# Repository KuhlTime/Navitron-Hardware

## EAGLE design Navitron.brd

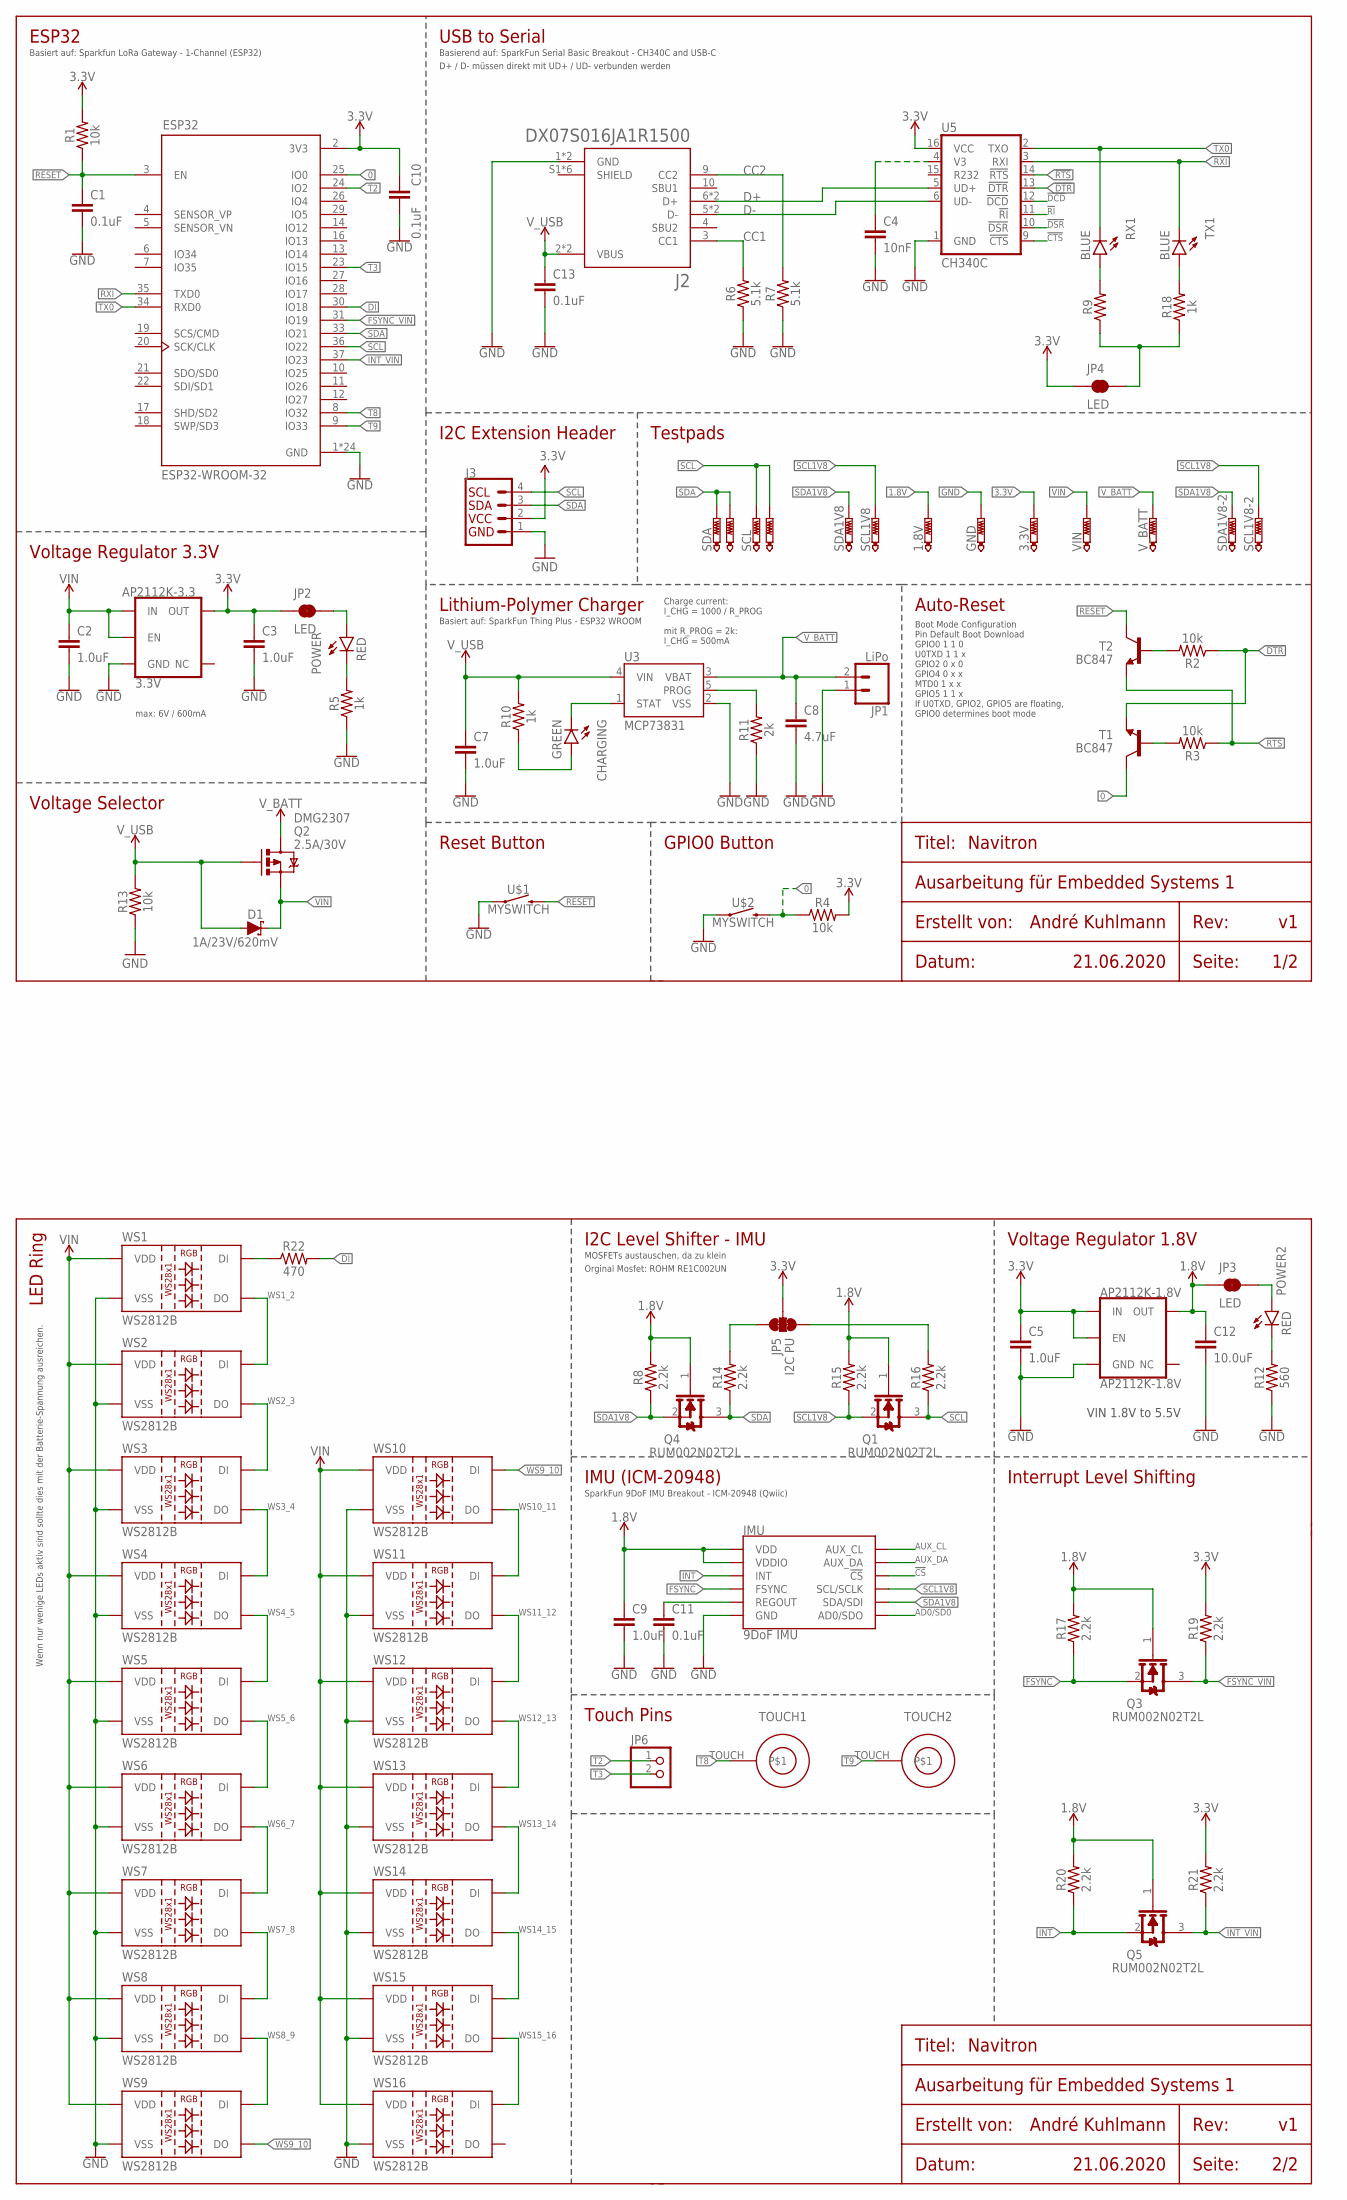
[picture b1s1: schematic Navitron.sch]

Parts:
1.8V, 3.3V: PTR1B1,27; B1,27
AP2112K-1.8V: AP2112K-1.8V; SOT23-5
AP2112K-3.3: 3.3V; SOT23-5
C1, C10, C11, C13: 0.1uF; 0603
C2, C3, C5, C7, C9: 1.0uF; 0603
C4: 10nF; 0603
C8: 4.7uF; 0603
C12: 10.0uF; 0603
CHARGING: GREEN; LED-0603
D1: 1A/23V/620mV; SOD-323
ESP32: ESP32-WROOM-32; MODULE_ESP32-WROOM-32
GND: PTR1B1,27; B1,27
IMU: 9DoF IMU; QFN24-3X3-ICM-20948
J2: DX07S016JA1R1500; JAE_DX07S016JA1R1500
J3: QWIIC_CONNECTORJS-1MM; 1X04_1MM_RA
JP1: LiPo; JST-2-SMD
JP2, JP3, JP4: LED; SMT-JUMPER_2_NC_TRACE_SILK
JP5: I2C PU; SMT-JUMPER_3_2-NC_TRACE_SILK
JP6: PINHD-1X2; 1X02
POWER, POWER2: RED; LED-0603
Q1, Q3, Q4, Q5: ROHM_RUM002N02T2LROHM_RUM002N02T2L_0_0; ROHM_RUM002N02T2L_0
Q2: 2.5A/30V; SOT23-3@1
R1, R2, R3, R4, R13: 10k; 0603
R5, R10, R18: 1k; 0603
R6, R7: 5.1k; 0603
R8, R14, R15, R16, R17, R19, R20, R21: 2.2k; 0603
R9: 10MOHM-0603-1/10W-5%; 0603
R11: 2k; 0603
R12: 560; 0603
R22: 470; 0603
RX1: BLUE; LED-0603
SCL, SCL1, SCL1V8, SCL1V8-2: PTR1B1,27; B1,27
SDA, SDA1, SDA1V8, SDA1V8-2: PTR1B1,27; B1,27
T1, T2: BC847; SOT23
TOUCH1, TOUCH2: TOUCHPAD8MM; TOUCHPAD-8MM
TX1: BLUE; LED-0603
U3: MCP73831; SOT23-5
U5: CH340C; SO016
U$1, U$2: MYSWITCH; MY-BUTTON
VIN: PTR1B1,27; B1,27
V_BATT: PTR1B1,27; B1,27
WS1, WS2, WS3, WS4, WS5, WS6, WS7, WS8, WS9, WS10, WS11, WS12, WS13, WS14, WS15, WS16: WS2812B

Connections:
0: ESP32.25 (IO0), R4.1, T1.3 (C), U$2.P$2 (2)
1.8V: 1.8V.TP, AP2112K-1.8V.5 (OUT), C9.1, C12.1, IMU.8 (VDDIO), IMU.13 (VDD), JP3.1, Q1.1 (GATE), Q3.1 (GATE), Q4.1 (GATE), Q5.1 (GATE), R8.2, R15.2, R17.2, R20.2
3.3V: 3.3V.TP, AP2112K-1.8V.1 (IN), AP2112K-1.8V.3 (EN), AP2112K-3.3.5 (OUT), C3.1, C5.1, C10.1, ESP32.2 (3V3), J3.2, JP2.1, JP4.1, JP5.2, R1.2, R4.2, R19.2, R21.2, U5.16 (VCC)
!CS: IMU.22 (!CS)
!CTS: U5.9 (!CTS)
!DCD: U5.12 (!DCD)
!DSR: U5.10 (!DSR)
!DTR: R2.1, T1.2 (E), U5.13 (!DTR)
!RI: U5.11 (!RI)
!RTS: R3.1, T2.2 (E), U5.14 (!RTS)
AD0/SD0: IMU.9 (AD0/SDO)
AUX_CL: IMU.7 (AUX_CL)
AUX_DA: IMU.21 (AUX_DA)
CC1: J2.3 (CC1), R6.2
CC2: J2.9 (CC2), R7.2
CHAR_LED_VIN: CHARGING.A, R10.1
D+: J2.6 (D+), J2.7 (D+), U5.5 (UD+)
D-: J2.5 (D-), J2.8 (D-), U5.6 (UD-)
DI: ESP32.30 (IO18), R22.2
DI_TO_WS: R22.1, WS1.4 (DI)
FSYNC: IMU.11 (FSYNC), Q3.2 (SOURCE), R17.1
FSYNC_VIN: ESP32.31 (IO19), Q3.3 (DRAIN), R19.1
GND: AP2112K-1.8V.2 (GND), AP2112K-3.3.2 (GND), C1.2, C2.2, C3.2, C4.2, C5.2, C7.2, C8.2, C9.2, C10.2, C11.2, C12.2, C13.2, ESP32.1 (GND), ESP32.15 (GND), ESP32.38 (GND), ESP32.39_1 (GND), ESP32.39_2 (GND), ESP32.39_3 (GND), ESP32.39_4 (GND), ESP32.39_5 (GND), ESP32.39_6 (GND), ESP32.39_7 (GND), ESP32.39_8 (GND), ESP32.39_9 (GND), ESP32.39_10 (GND), ESP32.39_11 (GND), ESP32.39_12 (GND), ESP32.39_13 (GND), ESP32.39_14 (GND), ESP32.39_15 (GND), ESP32.39_16 (GND), ESP32.39_17 (GND), ESP32.39_18 (GND), ESP32.39_19 (GND), ESP32.39_20 (GND), ESP32.39_21 (GND), GND.TP, IMU.18 (GND), IMU.20 (GND), J2.1 (GND), J2.12 (GND), J3.1, JP1.1 (2), R5.1, R6.1, R7.1, R11.1, R12.1, R13.1, U3.2 (VSS), U5.1 (GND), U$1.P$1 (1), U$2.P$1 (1), WS1.3 (VSS), WS2.3 (VSS), WS3.3 (VSS), WS4.3 (VSS), WS5.3 (VSS), WS6.3 (VSS), WS7.3 (VSS), WS8.3 (VSS), WS9.3 (VSS), WS10.3 (VSS), WS11.3 (VSS), WS12.3 (VSS), WS13.3 (VSS), WS14.3 (VSS), WS15.3 (VSS), WS16.3 (VSS)
INT: IMU.12 (INT), Q5.2 (SOURCE), R20.1
INT_VIN: ESP32.37 (IO23), Q5.3 (DRAIN), R21.1
LED1.8: JP3.2, POWER2.A
LED1.8_2: POWER2.C, R12.2
unnamed: POWER.C, R5.2
unnamed: JP2.2, POWER.A
PROG: R11.2, U3.5 (PROG)
REGOUT: C11.1, IMU.10 (REGOUT)
RESET: C1.1, ESP32.3 (EN), R1.1, T2.3 (C), U$1.P$2 (2)
RXI: ESP32.35 (TXD0), TX1.C, U5.3 (RXI)
SCL: ESP32.36 (IO22), J3.4, Q1.3 (DRAIN), R16.1, SCL.TP, SCL1.TP
SCL1V8: IMU.23 (SCL/SCLK), Q1.2 (SOURCE), R15.1, SCL1V8.TP, SCL1V8-2.TP
SDA: ESP32.33 (IO21), J3.3, Q4.3 (DRAIN), R14.1, SDA.TP, SDA1.TP
SDA1V8: IMU.24 (SDA/SDI), Q4.2 (SOURCE), R8.1, SDA1V8.TP, SDA1V8-2.TP
SDA_W_1: JP5.1, R14.2
SDA_W_2: JP5.3, R16.2
STAT: CHARGING.C, U3.1 (STAT)
T2: ESP32.24 (IO2), JP6.1
T3: ESP32.23 (IO15), JP6.2
T8: ESP32.8 (IO32), TOUCH1.TOUCH
T9: ESP32.9 (IO33), TOUCH2.TOUCH
TO_RX_LED: R18.2, TX1.A
TO_T1: R3.2, T1.1 (B)
TO_T2: R2.2, T2.1 (B)
TO_TX_LED: R9.2, RX1.A
TX0: ESP32.34 (RXD0), RX1.C, U5.2 (TXO)
TX_RX_LED_SUPPLY: JP4.2, R9.1, R18.1
V3_CH340: C4.1, U5.4 (V3)
VIN: AP2112K-3.3.1 (IN), AP2112K-3.3.3 (EN), C2.1, D1.C, Q2.2 (S), VIN.TP, WS1.1 (VDD), WS2.1 (VDD), WS3.1 (VDD), WS4.1 (VDD), WS5.1 (VDD), WS6.1 (VDD), WS7.1 (VDD), WS8.1 (VDD), WS9.1 (VDD), WS10.1 (VDD), WS11.1 (VDD), WS12.1 (VDD), WS13.1 (VDD), WS14.1 (VDD), WS15.1 (VDD), WS16.1 (VDD)
V_BATT: C8.1, JP1.2 (1), Q2.3 (D), U3.3 (VBAT), V_BATT.TP
V_USB: C7.1, C13.1, D1.A, J2.2 (VBUS), J2.11 (VBUS), Q2.1 (G), R10.2, R13.2, U3.4 (VIN)
WS1_2: WS1.2 (DO), WS2.4 (DI)
WS2_3: WS2.2 (DO), WS3.4 (DI)
WS3_4: WS3.2 (DO), WS4.4 (DI)
WS4_5: WS4.2 (DO), WS5.4 (DI)
WS5_6: WS5.2 (DO), WS6.4 (DI)
WS6_7: WS6.2 (DO), WS7.4 (DI)
WS7_8: WS7.2 (DO), WS8.4 (DI)
WS8_9: WS8.2 (DO), WS9.4 (DI)
WS9_10: WS9.2 (DO), WS10.4 (DI)
WS10_11: WS10.2 (DO), WS11.4 (DI)
WS11_12: WS11.2 (DO), WS12.4 (DI)
WS12_13: WS12.2 (DO), WS13.4 (DI)
WS13_14: WS13.2 (DO), WS14.4 (DI)
WS14_15: WS14.2 (DO), WS15.4 (DI)
WS15_16: WS15.2 (DO), WS16.4 (DI)

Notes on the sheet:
Seite:
1/2
Datum:
21.06.2020
Erstellt von:
André Kuhlmann
Rev:
Ausarbeitung für Embedded Systems 1
Navitron
Titel:
Boot Mode Configuration Pin Default Boot Download GPIO0 1 1 0 U0TXD 1 1 x GPIO2 0 x 0 GPIO4 0 x x MTD0 1 x x GPIO5 1 1 x If U0TXD, GPIO2, GPIO5 are floating, GPIO0 determines boot mode
Basiert auf: Sparkfun LoRa Gateway - 1-Channel (ESP32)
Voltage Regulator 3.3V
ESP32
Auto-Reset
USB to Serial
max: 6V / 600mA
D+ / D- müssen direkt mit UD+ / UD- verbunden werden
Basierend auf: SparkFun Serial Basic Breakout - CH340C and USB-C
Reset Button
GPIO0 Button
Voltage Selector
Lithium-Polymer Charger
Basiert auf: SparkFun Thing Plus - ESP32 WROOM
Charge current: I_CHG = 1000 / R_PROG mit R_PROG = 2k: I_CHG = 500mA
I2C Extension Header
VIN 1.8V to 5.5V
Voltage Regulator 1.8V
IMU (ICM-20948)
2/2
LED Ring
I2C Level Shifter - IMU
Wenn nur wenige LEDs aktiv sind sollte dies mit der Batterie-Spannung ausreichen.
MOSFETs austauschen, da zu klein
SparkFun 9DoF IMU Breakout - ICM-20948 (Qwiic)
Orginal Mosfet: ROHM RE1C002UN
Interrupt Level Shifting
Testpads
Touch Pins
DMG2307

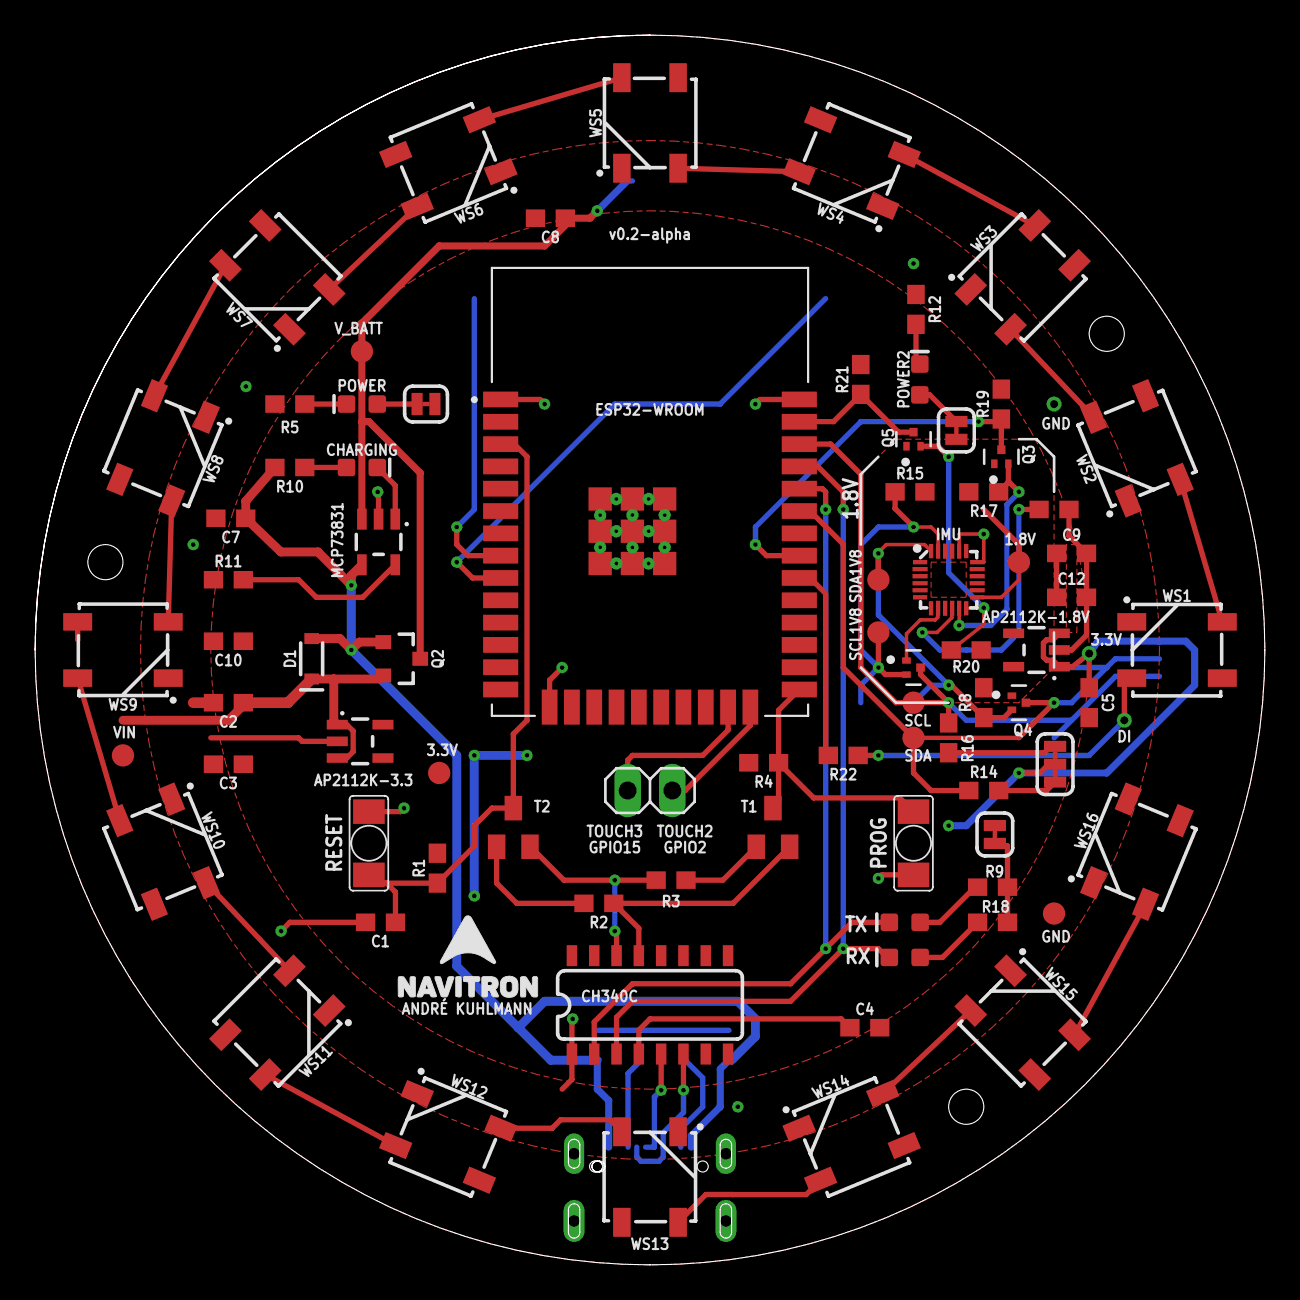
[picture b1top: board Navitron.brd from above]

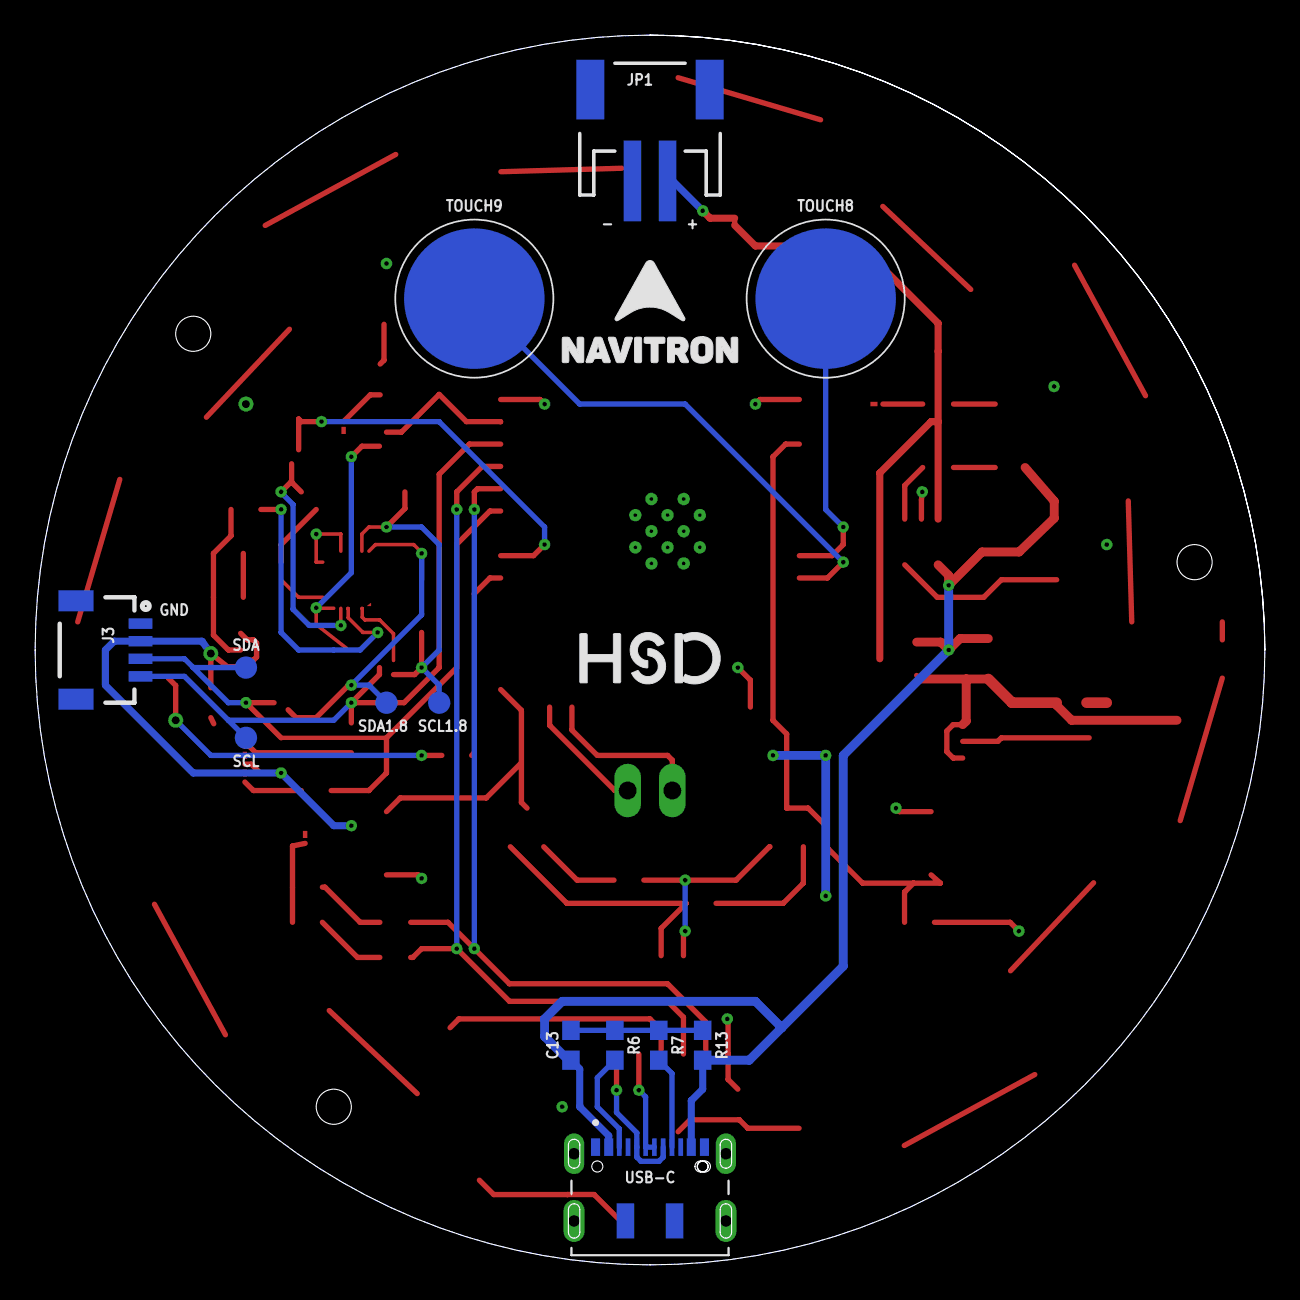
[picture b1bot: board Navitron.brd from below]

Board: 2 copper layers, 70.0 x 70.0 mm, 94 parts (13 on the bottom side), 61 nets.

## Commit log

2020-07-15 Replace 403 Resistors with 603 Resistors
2020-07-15 Inspected
2020-07-19 Pad Renaming
2020-07-25 Change Voltage Regulator and Resistor Value
2020-07-25 Change C5 Position
    - Moved Capacitor closer to the 1.8V Voltage Regulator.
2020-07-25 Add Todolist
2020-07-25 Fix Todo Formatting
2020-07-25 Add Testingpoints
    Added Testingpoints for:
    - GND
    - 3.3V
    - 1.8V
    - SDA
    - SCL
2020-07-26 fix #1
    - Fixed the heatsink, of the ICM-20948 briding the FSYNC and INT lines
2020-07-26 Remove Temporary Button
2020-07-28 Tented Vias + Some Changes
2020-07-28 Touchpads and Logos
    - Added Touchpads
    - Add Logos
2020-07-28 Connect Touch Pad 8 & 9 and DRC Check
2020-07-28 Add Additional 1.8V SDA and SCL Pad
2020-07-28 Change Bottom Logo Position
2020-07-28 Cleanup 3.3V Power Circuit
2020-07-30 Small changes
2020-08-10 Change Revision Number
2020-08-10 Add Review Material

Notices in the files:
parts and their libraries:
SparkFun-IC-Power: Licensing: Creative Commons ShareAlike 4.0 International - https://creativecommons.org/licenses/by-sa/4.0
